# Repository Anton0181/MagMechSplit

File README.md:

# MagMechSplit
Small project just for fun with trying to develop a split keyboard that can handle both mech and tmr switches and all that wireless

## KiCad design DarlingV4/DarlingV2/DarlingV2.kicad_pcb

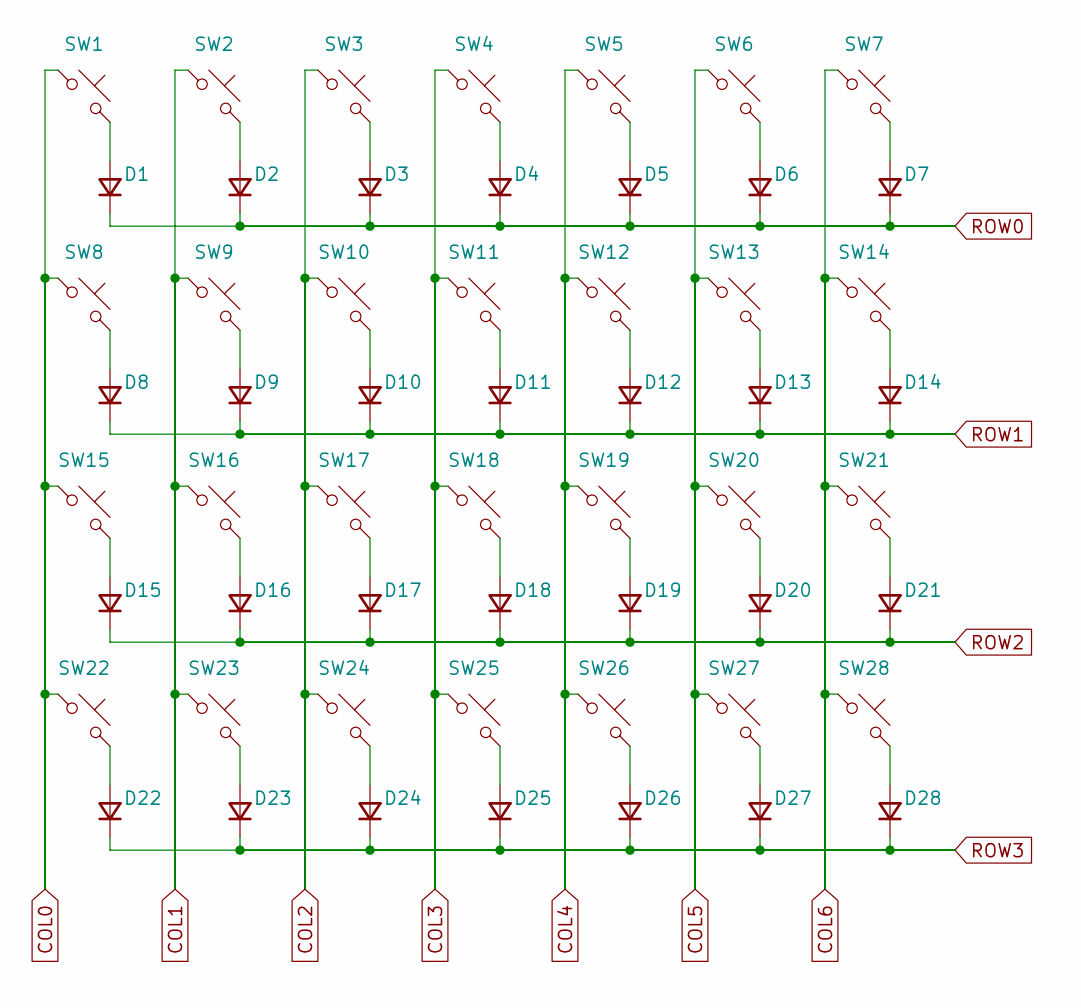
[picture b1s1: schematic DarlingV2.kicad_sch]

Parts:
D1, D2, D3, D4, D5, D6, D7, D8, D9, D10, D11, D12, D13, D14, D15, D16, D17, D18, D19, D20, D21, D22, D23, D24, D25, D26, D27, D28: D; D_SOD-123
SW1, SW2, SW3, SW4, SW5, SW6, SW8, SW9, SW10, SW11, SW12, SW13, SW15, SW16, SW17, SW18, SW19, SW20, SW22, SW23, SW24, SW25, SW26, SW27, SW28: SW_Push; SW_Hotswap_Kailh_Choc_V1V2_1.00u
SW7, SW14, SW21: SW_Push; SW_Hotswap_Kailh_Choc_V1V2_1.25u

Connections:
COL0: SW1.1, SW8.1, SW15.1, SW22.1
COL1: SW2.1, SW9.1, SW16.1, SW23.1
COL2: SW3.1, SW10.1, SW17.1, SW24.1
COL3: SW4.1, SW11.1, SW18.1, SW25.1
COL4: SW5.1, SW12.1, SW19.1, SW26.1
COL5: SW6.1, SW13.1, SW20.1, SW27.1
COL6: SW7.1, SW14.1, SW21.1, SW28.1
unnamed: D1.2 (A), SW1.2
unnamed: D2.2 (A), SW2.2
unnamed: D3.2 (A), SW3.2
unnamed: D4.2 (A), SW4.2
unnamed: D5.2 (A), SW5.2
unnamed: D6.2 (A), SW6.2
unnamed: D7.2 (A), SW7.2
unnamed: D8.2 (A), SW8.2
unnamed: D9.2 (A), SW9.2
unnamed: D10.2 (A), SW10.2
unnamed: D11.2 (A), SW11.2
unnamed: D12.2 (A), SW12.2
unnamed: D13.2 (A), SW13.2
unnamed: D14.2 (A), SW14.2
unnamed: D15.2 (A), SW15.2
unnamed: D16.2 (A), SW16.2
unnamed: D17.2 (A), SW17.2
unnamed: D18.2 (A), SW18.2
unnamed: D19.2 (A), SW19.2
unnamed: D20.2 (A), SW20.2
unnamed: D21.2 (A), SW21.2
unnamed: D22.2 (A), SW22.2
unnamed: D23.2 (A), SW23.2
unnamed: D24.2 (A), SW24.2
unnamed: D25.2 (A), SW25.2
unnamed: D26.2 (A), SW26.2
unnamed: D27.2 (A), SW27.2
unnamed: D28.2 (A), SW28.2
ROW0: D1.1 (K), D2.1 (K), D3.1 (K), D4.1 (K), D5.1 (K), D6.1 (K), D7.1 (K)
ROW1: D8.1 (K), D9.1 (K), D10.1 (K), D11.1 (K), D12.1 (K), D13.1 (K), D14.1 (K)
ROW2: D15.1 (K), D16.1 (K), D17.1 (K), D18.1 (K), D19.1 (K), D20.1 (K), D21.1 (K)
ROW3: D22.1 (K), D23.1 (K), D24.1 (K), D25.1 (K), D26.1 (K), D27.1 (K), D28.1 (K)

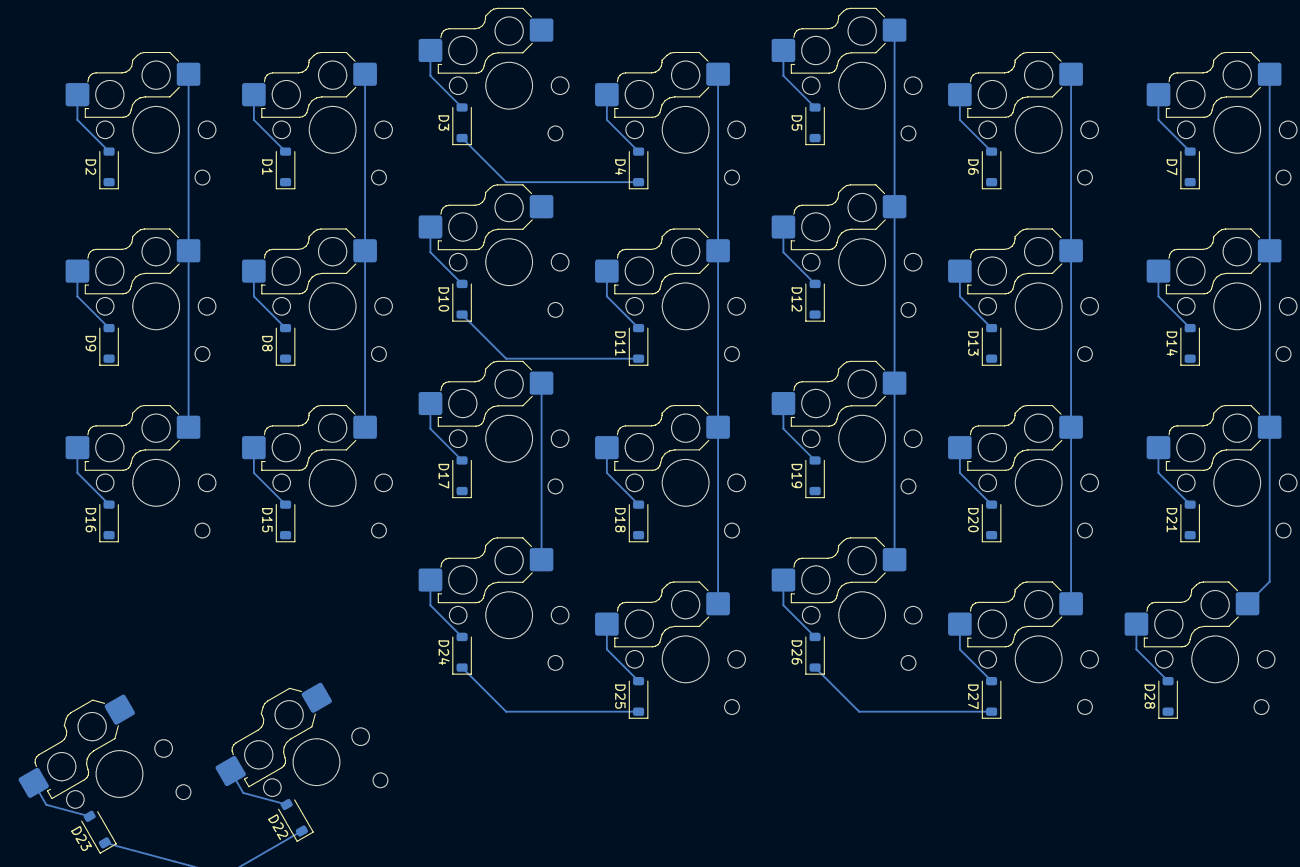
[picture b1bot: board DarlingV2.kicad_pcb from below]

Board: 2 copper layers, 56 parts (28 on the bottom side), 39 nets.

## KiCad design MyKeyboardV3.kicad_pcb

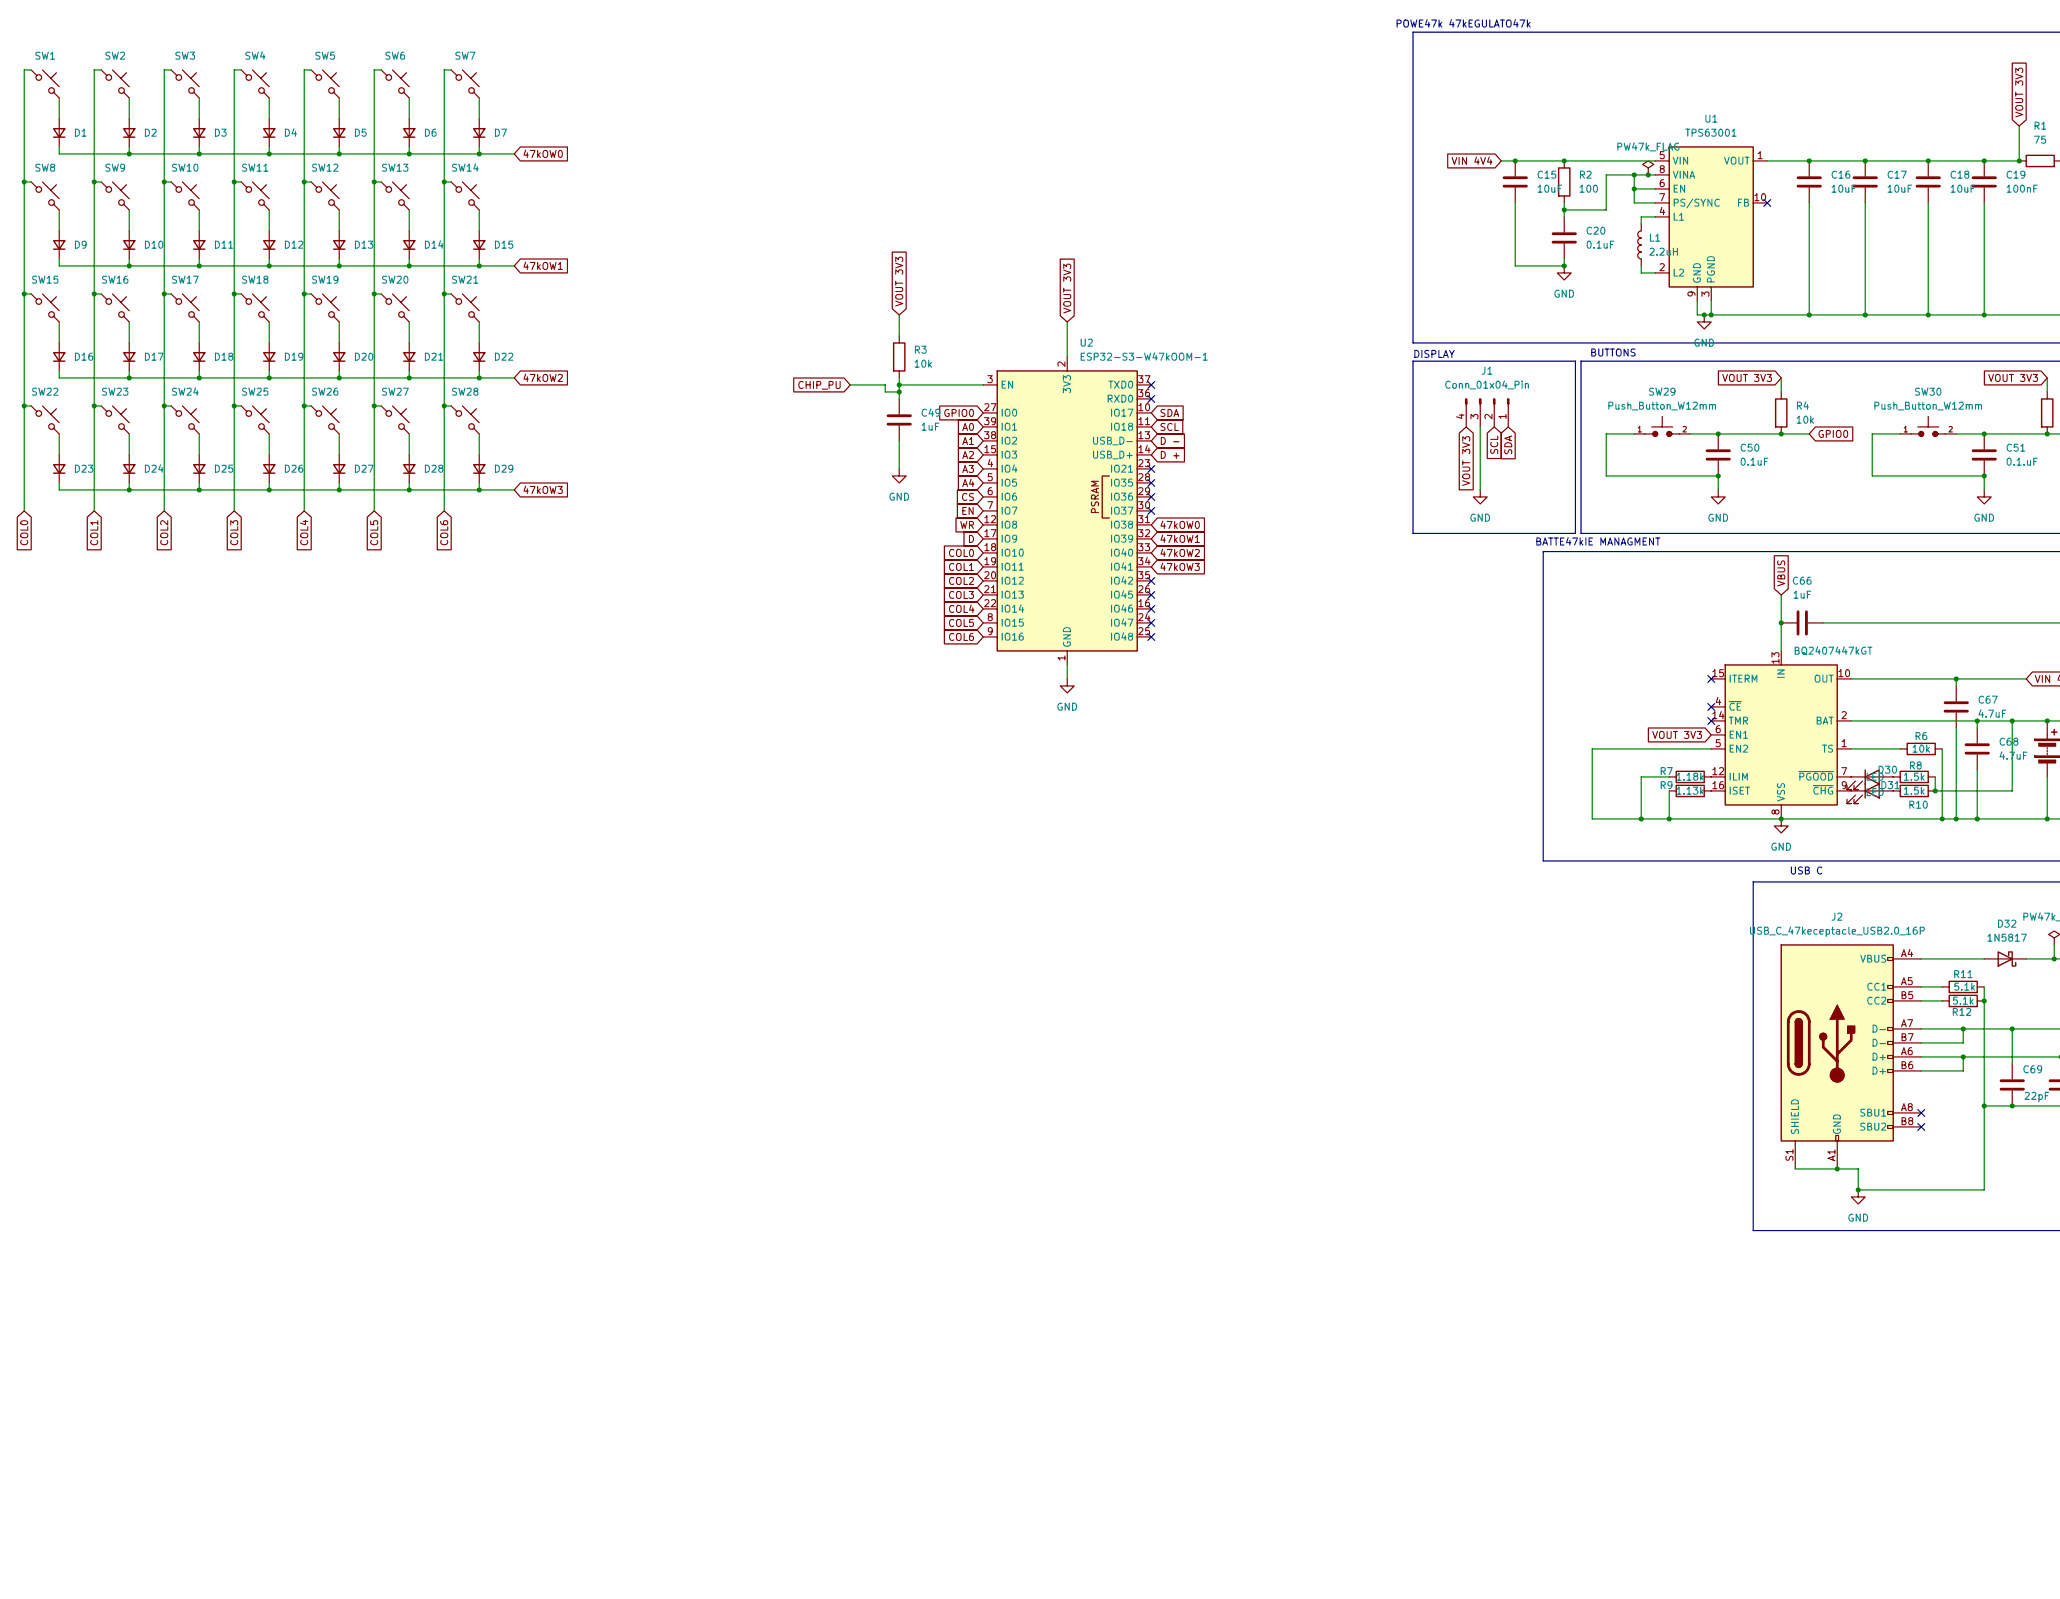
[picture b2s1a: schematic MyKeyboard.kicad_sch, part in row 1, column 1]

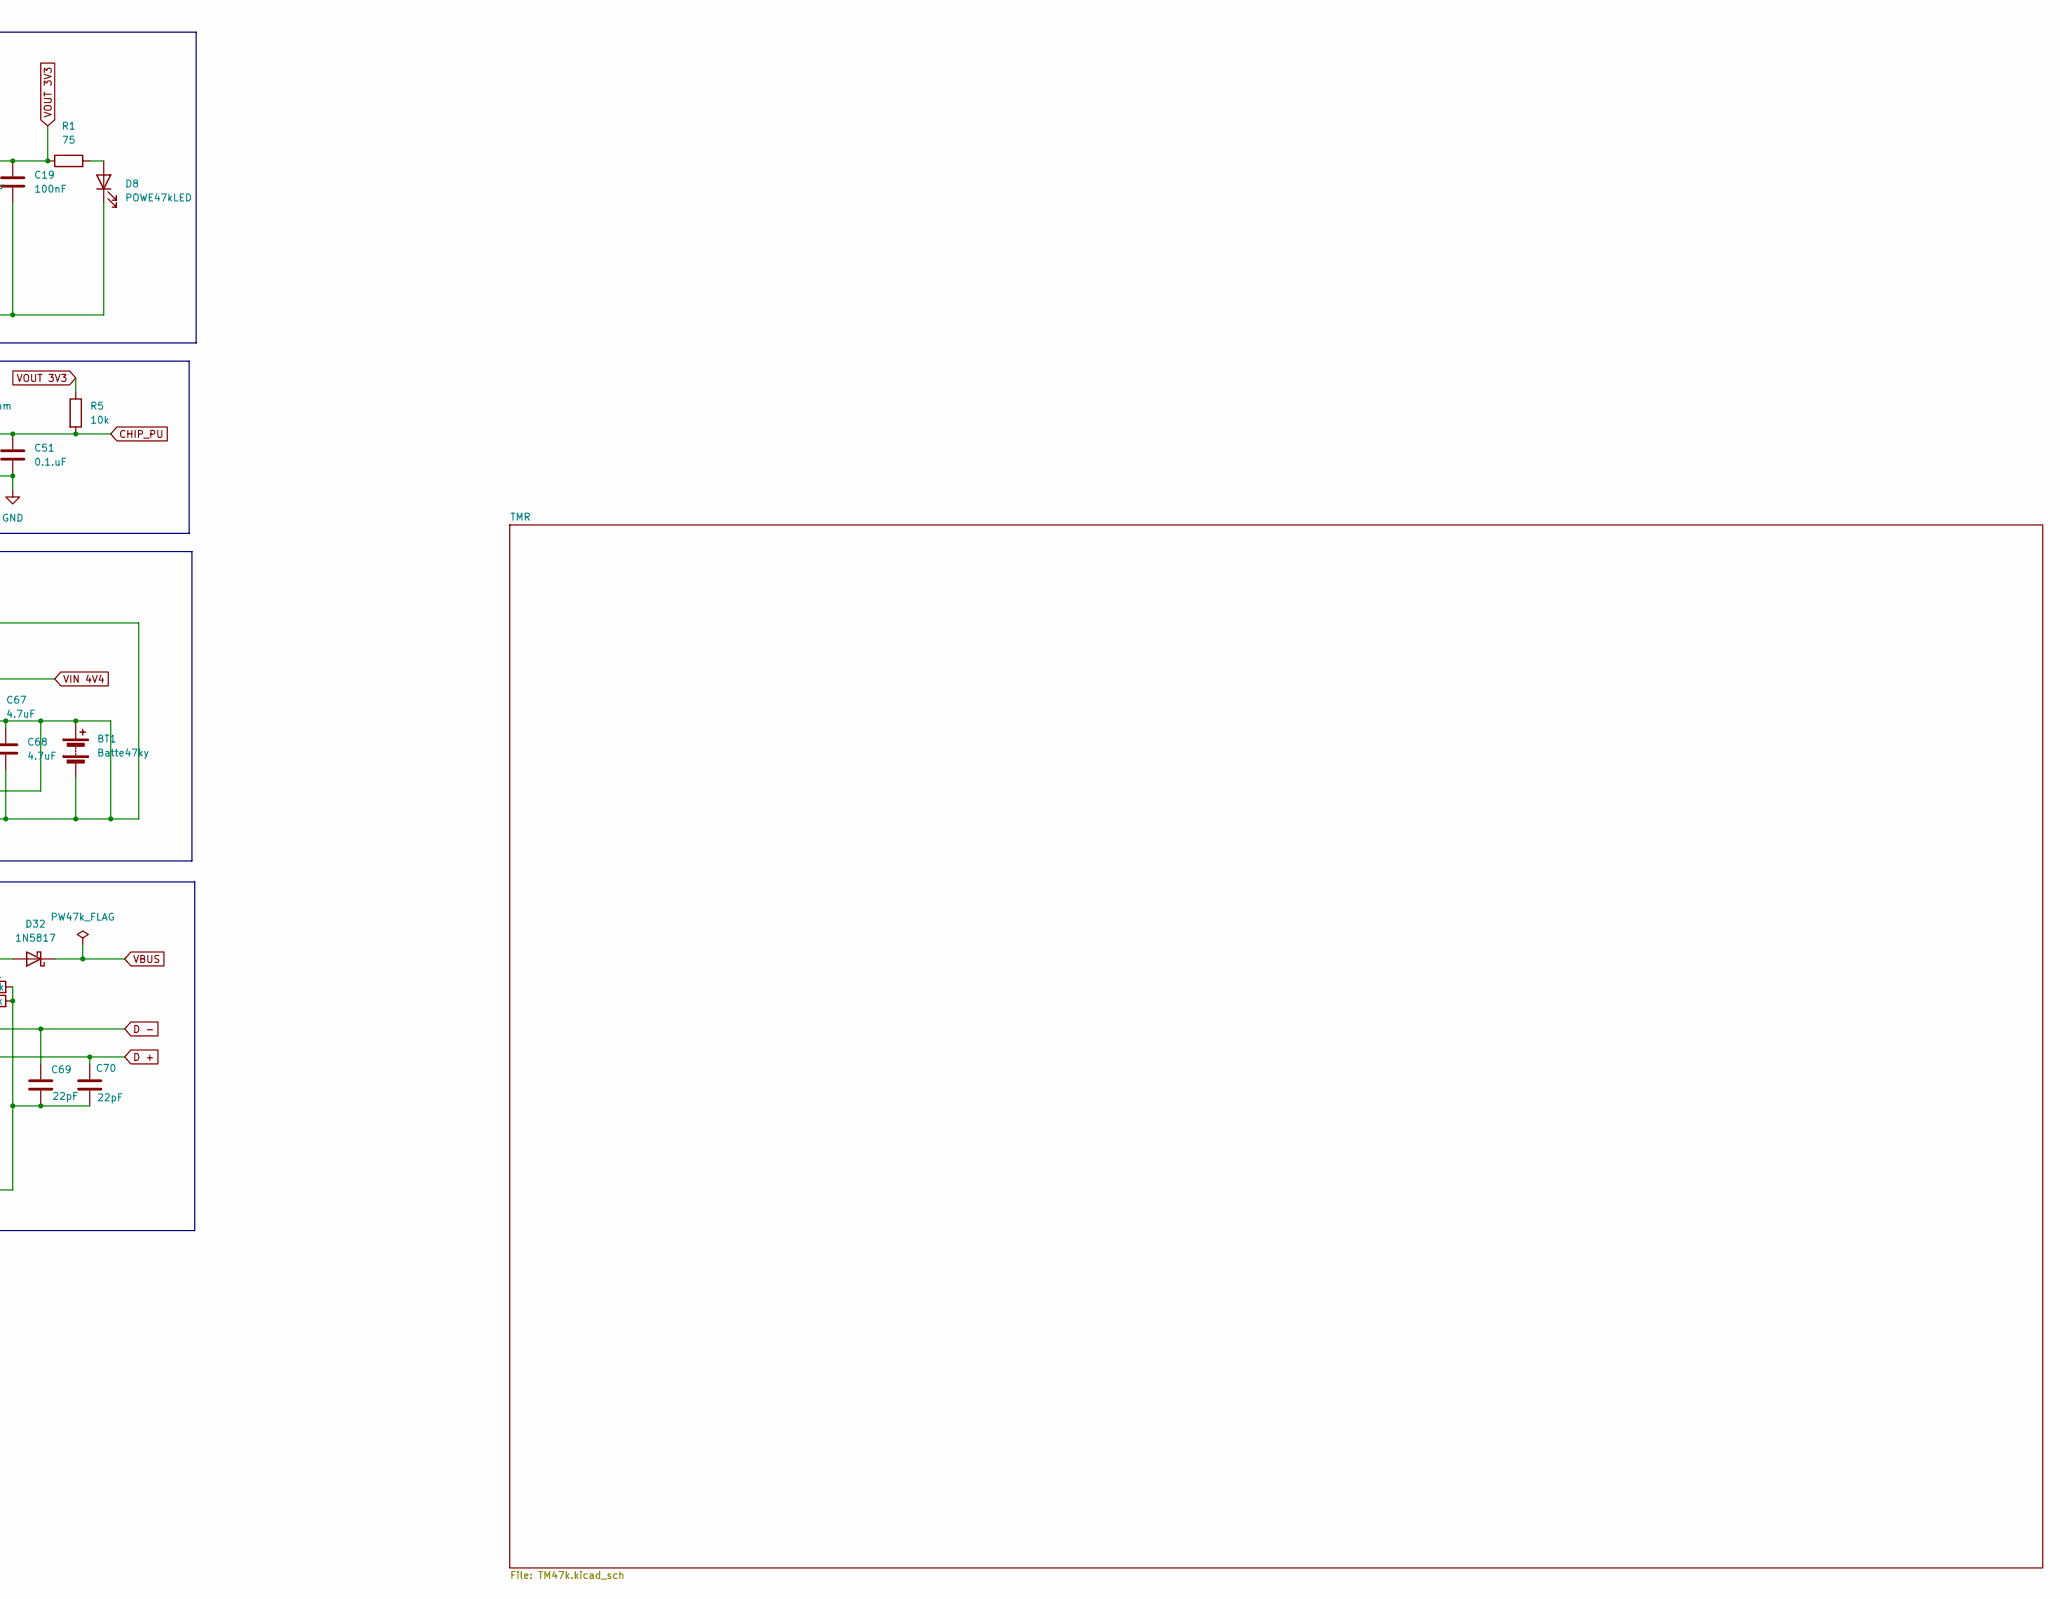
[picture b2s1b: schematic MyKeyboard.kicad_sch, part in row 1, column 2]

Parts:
BT1: Batte47ky; Battery
C15, C16, C17, C18: 10uF; CAPC1005X55N
C19: 100nF; CAPC1005X55N
C20, C50: 0.1uF; CAPC1005X55N
C49, C66: 1uF; CAPC3216X180N
C51: 0.1.uF; CAPC1005X55N
C67, C68: 4.7uF; CAPC2012X140N
C69, C70: 22pF; CAPC1608X90N
D1, D2, D3, D4, D5, D6, D7, D9, D10, D11, D12, D13, D14, D15, D16, D17, D18, D19, D20, D21, D22, D23, D24, D25, D26, D27, D28, D29: D; D_SOD-123F
D8: POWE47kLED; LED_0201_0603Metric
D30, D31: LED; LED_0201_0603Metric
D32: 1N5817; D_DO-41_SOD81_P10.16mm_Horizontal
J1: Conn_01x04_Pin; Wago_734-164_1x04_P3.50mm_Horizontal
J2: USB_C_47keceptacle_USB2.0_16P; USB_C_Receptacle_GCT_USB4105-xx-A_16P_TopMnt_Horizontal
L1: 2.2uH; L_6.3x6.3_H3
R1: 75; R_0402_1005Metric
R2: 100; R_0402_1005Metric
R3, R4, R5, R6: 10k; R_0402_1005Metric
R7: 1.18k; R_0402_1005Metric
R8, R10: 1.5k; R_0402_1005Metric
R9: 1.13k; R_0402_1005Metric
R11, R12: 5.1k; R_0402_1005Metric
SW1, SW8, SW15: SW_Push; Hotswap_Choc_V1V2_1.25u
SW2, SW3, SW4, SW5, SW6, SW7, SW9, SW10, SW11, SW12, SW13, SW14, SW16, SW17, SW18, SW19, SW20, SW21, SW22, SW23, SW24, SW25, SW26: SW_Push; Hotswap_Choc_V1V2_1.00u
SW27, SW28: SW_Push; Hotswap_Choc_V1V2_2.00u_90deg
SW29, SW30: Push_Button_W12mm
U1: TPS63001; Texas_DRC0010J_ThermalVias
U2: ESP32-S3-W47kOOM-1; ESP32-S3-WROOM-1
U3: BQ2407447kGT; VQFN-16-1EP_3x3mm_P0.5mm_EP1.6x1.6mm

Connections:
A0: U2.39 (IO1)
A1: U2.38 (IO2)
A2: U2.15 (IO3)
A3: U2.4 (IO4)
A4: U2.5 (IO5)
CHIP_PU: C49.1, C51.1, R3.2, R5.2, SW30.2, U2.3 (EN)
COL0: SW1.1, SW8.1, SW15.1, SW22.1, U2.18 (IO10)
COL1: SW2.1, SW9.1, SW16.1, SW23.1, U2.19 (IO11)
COL2: SW3.1, SW10.1, SW17.1, SW24.1, U2.20 (IO12)
COL3: SW4.1, SW11.1, SW18.1, SW25.1, U2.21 (IO13)
COL4: SW5.1, SW12.1, SW19.1, SW26.1, U2.22 (IO14)
COL5: SW6.1, SW13.1, SW20.1, SW27.1, U2.8 (IO15)
COL6: SW7.1, SW14.1, SW21.1, SW28.1, U2.9 (IO16)
CS: U2.6 (IO6)
D: U2.17 (IO9)
D +: C70.2, J2.A6 (D+), J2.B6 (D+), U2.14 (USB_D+)
D -: C69.2, J2.A7 (D-), J2.B7 (D-), U2.13 (USB_D-)
EN: U2.7 (IO7)
GND: BT1.1 (+), BT1.2 (-), C15.2, C16.2, C17.2, C18.2, C19.2, C20.2, C49.2, C50.2, C51.2, C66.1, C67.1, C68.1, C68.2, C69.1, C70.1, D8.1 (K), J1.3, J2.A1 (GND), J2.A12 (GND), J2.B1 (GND), J2.B12 (GND), J2.S1 (SHIELD), R6.2, R7.1, R8.2, R9.1, R10.2, R11.2, R12.2, SW29.1, SW30.1, U1.3 (PGND), U1.9 (GND), U1.11 (PGND), U2.1 (GND), U2.40 (GND), U2.41 (GND), U3.2 (BAT), U3.3 (BAT), U3.5 (EN2), U3.8 (VSS), U3.17 (VSS)
GPIO0: C50.1, R4.2, SW29.2, U2.27 (IO0)
unnamed: D1.2 (A), SW1.2
unnamed: D2.2 (A), SW2.2
unnamed: D3.2 (A), SW3.2
unnamed: D4.2 (A), SW4.2
unnamed: D5.2 (A), SW5.2
unnamed: D6.2 (A), SW6.2
unnamed: D7.2 (A), SW7.2
unnamed: D8.2 (A), R1.2
unnamed: D9.2 (A), SW8.2
unnamed: D10.2 (A), SW9.2
unnamed: D11.2 (A), SW10.2
unnamed: D12.2 (A), SW11.2
unnamed: D13.2 (A), SW12.2
unnamed: D14.2 (A), SW13.2
unnamed: D15.2 (A), SW14.2
unnamed: D16.2 (A), SW15.2
unnamed: D17.2 (A), SW16.2
unnamed: D18.2 (A), SW17.2
unnamed: D19.2 (A), SW18.2
unnamed: D20.2 (A), SW19.2
unnamed: D21.2 (A), SW20.2
unnamed: D22.2 (A), SW21.2
unnamed: D23.2 (A), SW22.2
unnamed: D24.2 (A), SW23.2
unnamed: D25.2 (A), SW24.2
unnamed: D26.2 (A), SW25.2
unnamed: D27.2 (A), SW26.2
unnamed: D28.2 (A), SW27.2
unnamed: D29.2 (A), SW28.2
unnamed: D30.2 (A), R8.1
unnamed: D30.1 (K), U3.7 (~PGOOD)
unnamed: D31.2 (A), R10.1
unnamed: D31.1 (K), U3.9 (~CHG)
unnamed: D32.2 (A), J2.A4 (VBUS), J2.A9 (VBUS), J2.B4 (VBUS), J2.B9 (VBUS)
unnamed: J2.A5 (CC1), R11.1
unnamed: J2.B5 (CC2), R12.1
unnamed: C20.1, R2.2, U1.6 (EN), U1.7 (PS/SYNC), U1.8 (VINA)
unnamed: L1.2, U1.4 (L1)
unnamed: L1.1, U1.2 (L2)
unnamed: R7.2, U3.12 (ILIM)
unnamed: R9.2, U3.16 (ISET)
unnamed: R6.1, U3.1 (TS)
ROW0: D1.1 (K), D2.1 (K), D3.1 (K), D4.1 (K), D5.1 (K), D6.1 (K), D7.1 (K), U2.31 (IO38)
ROW1: D9.1 (K), D10.1 (K), D11.1 (K), D12.1 (K), D13.1 (K), D14.1 (K), D15.1 (K), U2.32 (IO39)
ROW2: D16.1 (K), D17.1 (K), D18.1 (K), D19.1 (K), D20.1 (K), D21.1 (K), D22.1 (K), U2.33 (IO40)
ROW3: D23.1 (K), D24.1 (K), D25.1 (K), D26.1 (K), D27.1 (K), D28.1 (K), D29.1 (K), U2.34 (IO41)
SCL: J1.2, U2.11 (IO18)
SDA: J1.1, U2.10 (IO17)
VBUS: C66.2, D32.1 (K), U3.13 (IN)
VIN 4V4: C15.1, C67.2, R2.1, U1.5 (VIN), U3.10 (OUT), U3.11 (OUT)
VOUT 3V3: C16.1, C17.1, C18.1, C19.1, J1.4, R1.1, R3.1, R4.1, R5.1, U1.1 (VOUT), U2.2 (3V3), U3.6 (EN1)
WR: U2.12 (IO8)

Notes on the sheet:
USB C
BUTTONS
DISPLAY
POWE47k 47kEGULATO47k
BATTE47kIE MANAGMENT

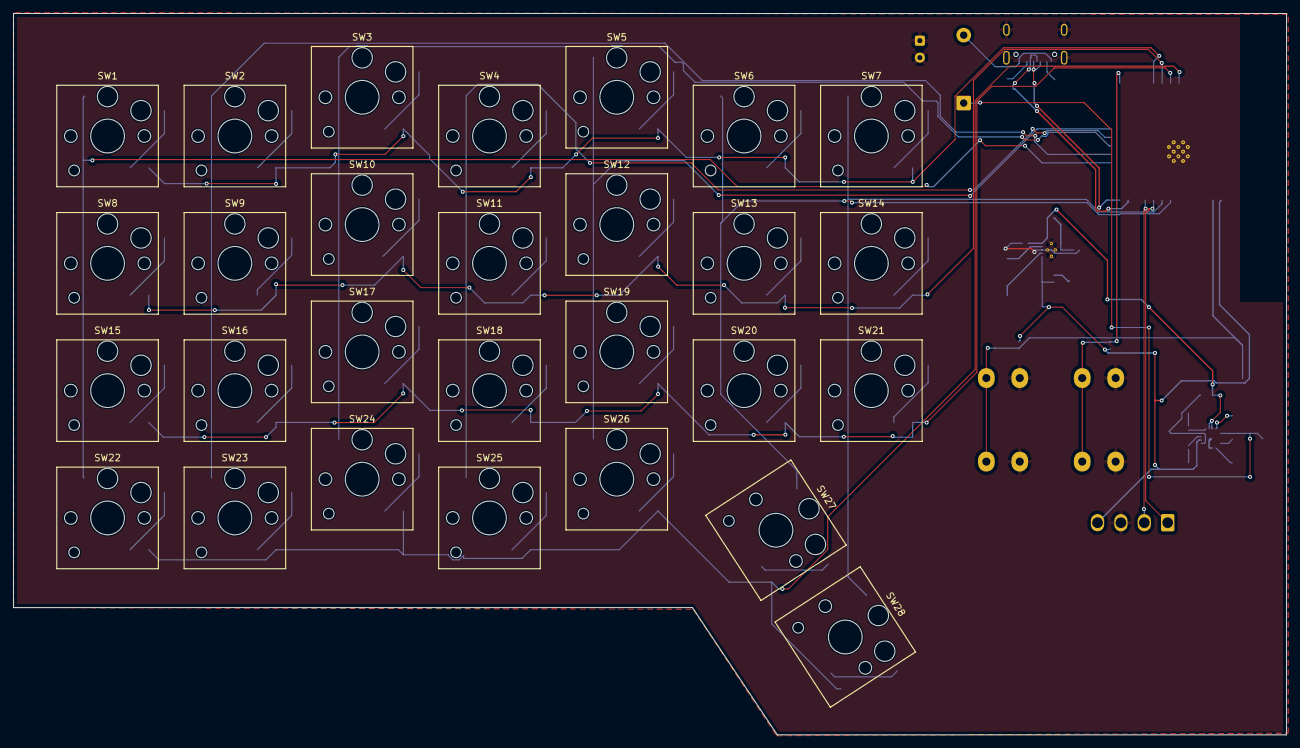
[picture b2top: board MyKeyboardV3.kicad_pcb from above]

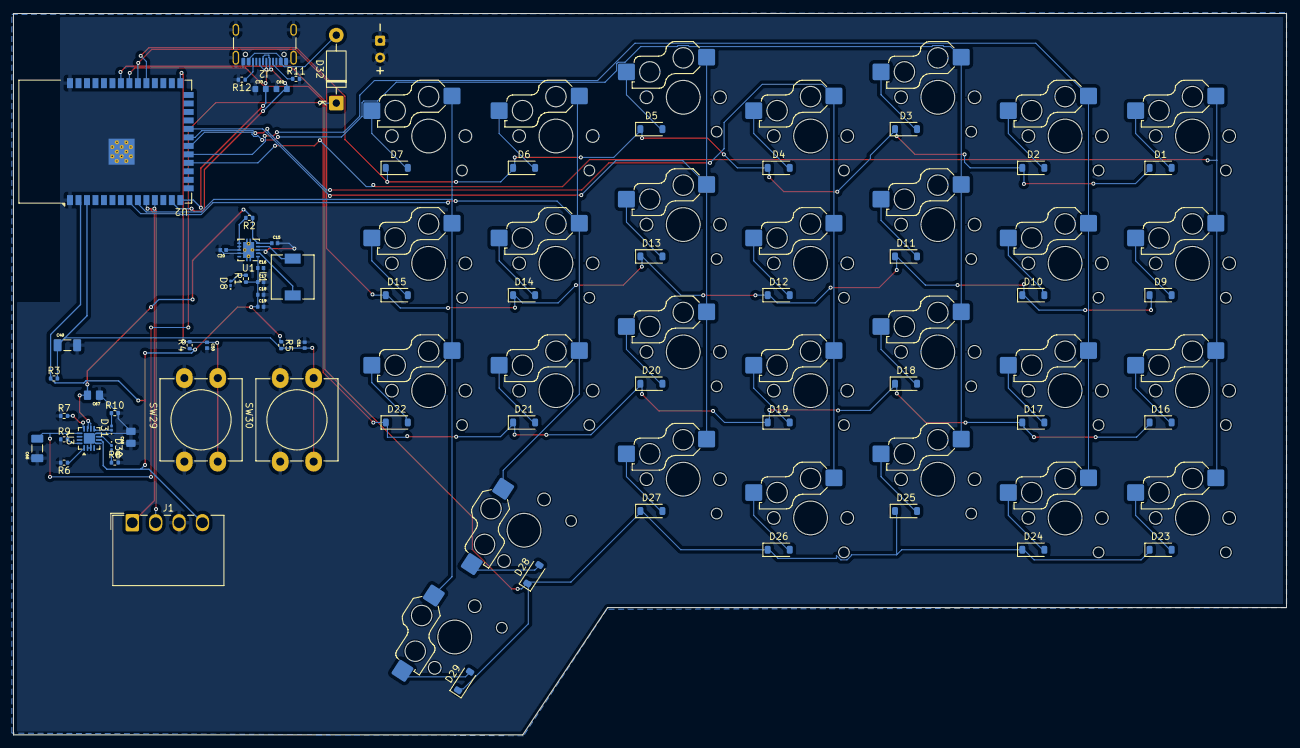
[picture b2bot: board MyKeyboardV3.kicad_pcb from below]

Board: 4 copper layers, 190.5 x 107.9 mm, 95 parts (67 on the bottom side), 63 nets.

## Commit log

2026-03-20 init commit
2026-03-22 new designs added
